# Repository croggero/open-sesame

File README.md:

# Open Sesame

ESP32-S3 firmware (Rust + esp-idf) for an assistive sliding door controller.

## Features

- Velocity-based assistive open/close
- Auto end-stop calibration and optional close-side homing
- Stall detection (obstacle / end-stop)
- Home Assistant MQTT discovery; commands, state and telemetry topics
- Captive-portal provisioning, factory reset via GPIO 0
- Build-time hardware/tuning configuration in `config.toml`

## Hardware

- ESP32-S3
- DRV8874 H-bridge (PhEn or InIn mode, set in `config.toml`)
- Quadrature encoder on the door drive
- Status LED, factory-reset button, optional toggle button

Pin assignments live under `[pins]` in `config.toml`.

## Building

Requires the Espressif Rust toolchain. See https://docs.esp-rs.org/book/installation/ for setup details.

1. Install `espup` and the `esp` toolchain:
   ```bash
   cargo install espup
   espup install
   ```
2. Source the export script in your shell (path printed by `espup install`):
   ```bash
   . $HOME/export-esp.sh
   ```
3. Install the flashing tools:
   ```bash
   cargo install espflash ldproxy
   ```
4. Edit `config.toml` to match your hardware (pins, motor mode, tuning).
5. Build:
   ```bash
   cargo build --release
   ```
6. Flash a connected ESP32 and open a serial monitor:
   ```bash
   cargo run --release
   ```
   Or, to flash with probe-rs and attach a debugger:
   ```bash
   cargo embed --release
   ```
  Or
  ```bash
  cargo flash --release --chip esp32s3
  ```

## First boot

1. Power the board. The status LED flashes to indicate the captive portal is active.
2. Connect to the `Open Sesame` SoftAP from a phone or laptop.
3. Submit WiFi and MQTT credentials in the provisioning form. The device reboots and connects.
4. The door is now visible in Home Assistant via MQTT discovery.

To re-provision, hold the factory-reset button (GPIO 0) for 5 seconds.

## Layout

- `src/main.rs` — boot sequence and control loop
- `src/door_controller.rs` — state machine, calibration, stall handling
- `src/motor.rs` — DRV8874 PWM driver (LEDC, 20 kHz)
- `src/encoder.rs` — PCNT quadrature decoder with 32-bit overflow tracking
- `src/mqtt_client.rs` — MQTT wrapper and command thread
- `src/captive_portal.rs` — SoftAP + HTTP provisioning
- `src/config.rs` — NVS-backed runtime config and build-time constants
- `config.toml` — hardware and tuning constants, parsed by `build.rs`

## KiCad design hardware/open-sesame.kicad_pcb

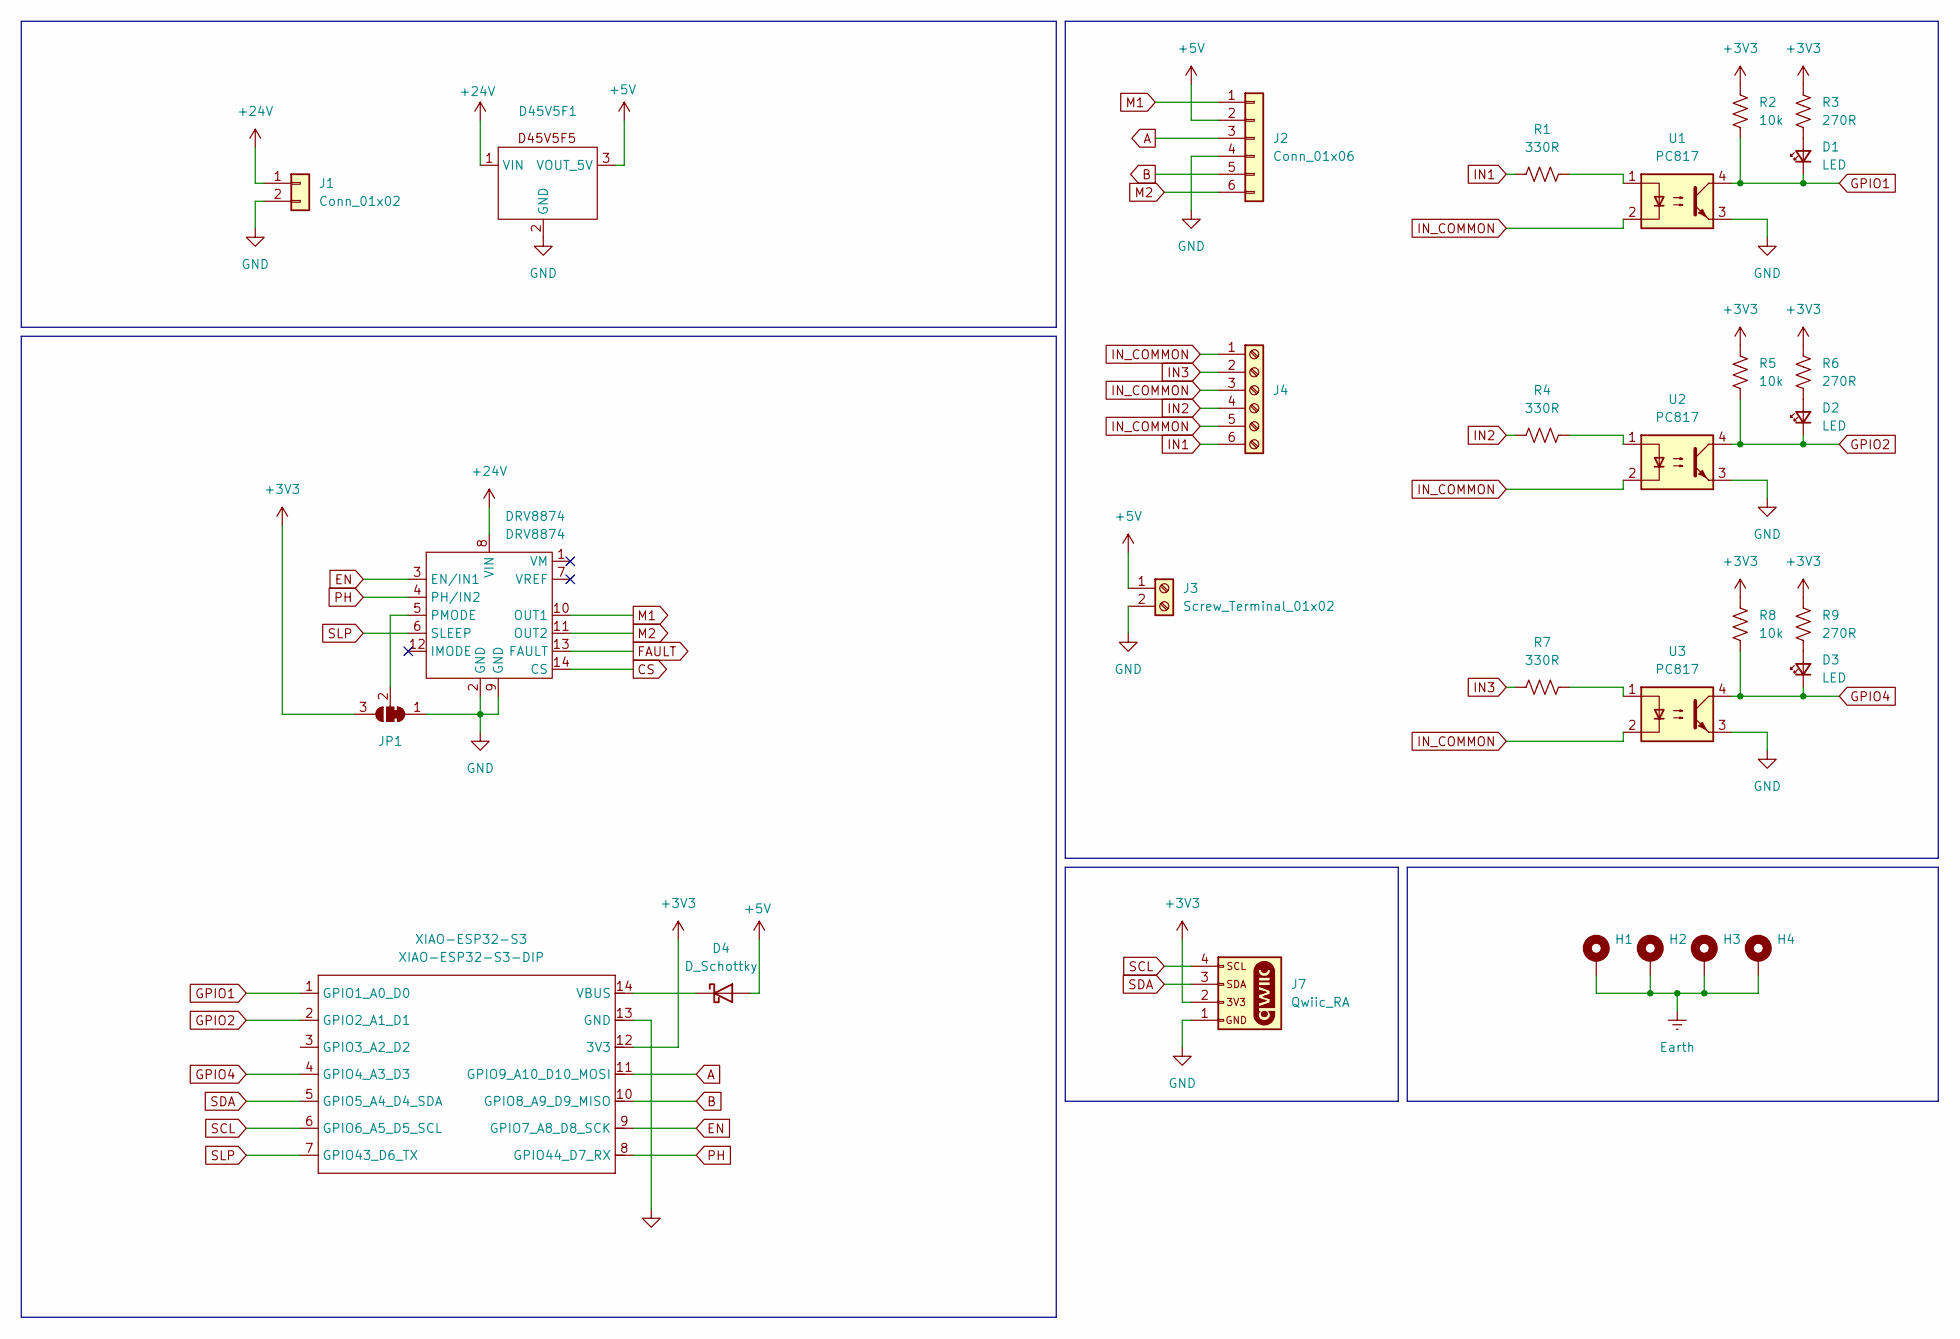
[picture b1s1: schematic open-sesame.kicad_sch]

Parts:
D1, D2, D3: LED; LED_0603_1608Metric
D4: D_Schottky; D_0603_1608Metric_Pad1.05x0.95mm_HandSolder
D45V5F1: D45V5F5; D45V5Fx
DRV8874: DRV8874
H1, H2, H3, H4: MountingHole_Pad; MountingHole_2.5mm_Pad_Via
J1: Conn_01x02; Molex_Nano-Fit_105313-xx02_1x02_P2.50mm_Horizontal
J2: Conn_01x06; Molex_Nano-Fit_105313-xx06_1x06_P2.50mm_Horizontal
J3: Screw_Terminal_01x02; TerminalBlock_Phoenix_MPT-0,5-2-2.54_1x02_P2.54mm_Horizontal
J4: Screw_Terminal_01x06; TerminalBlock_Phoenix_MPT-0,5-6-2.54_1x06_P2.54mm_Horizontal
J7: Qwiic_RA; JST_1x04_P1.0mm_Horizontal_SMD
JP1: SolderJumper_3_Bridged12; SolderJumper-3_P1.3mm_Bridged2Bar12_Pad1.0x1.5mm
R1, R4, R7: 330R; R_0603_1608Metric
R2, R5, R8: 10k; R_0603_1608Metric
R3, R6, R9: 270R; R_0603_1608Metric
U1, U2, U3: PC817; DIP-4_W7.62mm
XIAO-ESP32-S3: XIAO-ESP32-S3-DIP

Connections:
+3V3: J7.2, JP1.3 (B), R2.1, R3.1, R5.1, R6.1, R8.1, R9.1, XIAO-ESP32-S3.12 (3V3)
+5V: D4.2 (A), D45V5F1.3 (VOUT_5V), J2.2, J3.1
+24V: D45V5F1.1 (VIN), DRV8874.8 (VIN), J1.1
A: J2.3, XIAO-ESP32-S3.11 (GPIO9_A10_D10_MOSI)
B: J2.5, XIAO-ESP32-S3.10 (GPIO8_A9_D9_MISO)
CS: DRV8874.14 (CS)
EN: DRV8874.3 (EN/IN1), XIAO-ESP32-S3.9 (GPIO7_A8_D8_SCK)
Earth: H1.1, H2.1, H3.1, H4.1
FAULT: DRV8874.13 (FAULT)
GND: D45V5F1.2 (GND), DRV8874.2 (GND), DRV8874.9 (GND), J1.2, J2.4, J3.2, J7.1, JP1.1 (A), U1.3, U2.3, U3.3, XIAO-ESP32-S3.13 (GND)
GPIO1: D1.1 (K), R2.2, U1.4, XIAO-ESP32-S3.1 (GPIO1_A0_D0)
GPIO2: D2.1 (K), R5.2, U2.4, XIAO-ESP32-S3.2 (GPIO2_A1_D1)
GPIO4: D3.1 (K), R8.2, U3.4, XIAO-ESP32-S3.4 (GPIO4_A3_D3)
IN1: J4.6, R1.1
IN2: J4.4, R4.1
IN3: J4.2, R7.1
IN_COMMON: J4.1, J4.3, J4.5, U1.2, U2.2, U3.2
M1: DRV8874.10 (OUT1), J2.1
M2: DRV8874.11 (OUT2), J2.6
unnamed: D1.2 (A), R3.2
unnamed: D2.2 (A), R6.2
unnamed: D3.2 (A), R9.2
unnamed: D4.1 (K), XIAO-ESP32-S3.14 (VBUS)
unnamed: DRV8874.5 (PMODE), JP1.2 (C)
unnamed: R1.2, U1.1
unnamed: R4.2, U2.1
unnamed: R7.2, U3.1
PH: DRV8874.4 (PH/IN2), XIAO-ESP32-S3.8 (GPIO44_D7_RX)
SCL: J7.4, XIAO-ESP32-S3.6 (GPIO6_A5_D5_SCL)
SDA: J7.3, XIAO-ESP32-S3.5 (GPIO5_A4_D4_SDA)
SLP: DRV8874.6 (SLEEP), XIAO-ESP32-S3.7 (GPIO43_D6_TX)

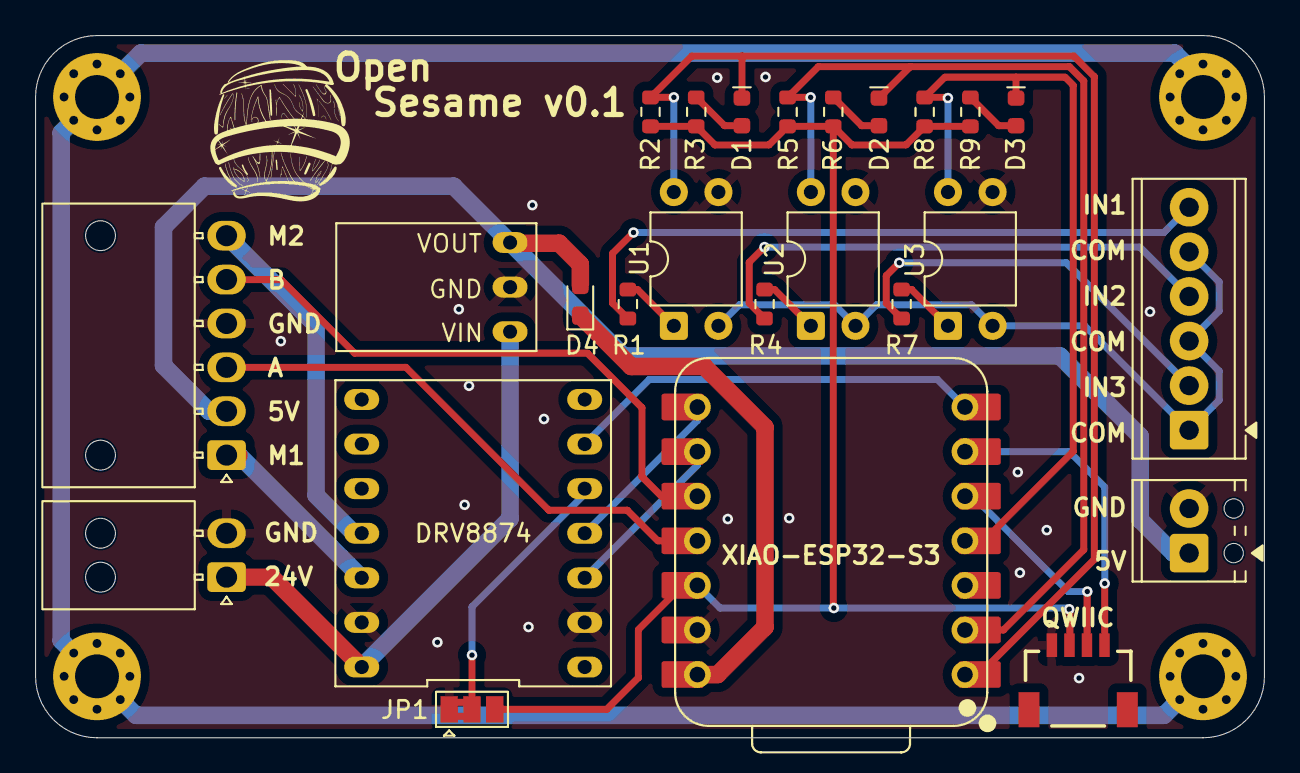
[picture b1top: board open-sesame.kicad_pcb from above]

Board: 2 copper layers, 70.0 x 40.0 mm, 29 parts (0 on the bottom side), 29 nets.

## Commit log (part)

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2026-02-05 Initial hardware circuit
2026-02-05 Added .gitignore
2026-02-05 Updated 3V & GND to terminal block
2026-02-05 fix(hardware): Corrected VIN&VOUT
2026-02-25 User Terminals, Added Optocoupler, Added QWIIC connector
2026-02-25 Use 2x 6 port connectors
2026-02-28 hardware: Use ESP32S3 for PCNT,
2026-03-02 hardware: shrunk board
2026-03-06 hardware: Use screw connectors and PC817
2026-03-24 hardware: use one power converter, shrink size, change connectors
2026-03-27 firmware: Initial Firmware
2026-03-31 firmware: Added calibration, obstacle stall detection, HA discovery, toggle pin
2026-03-31 firmware: set position via percentage
2026-03-31 firmware: fix invert direction, added homing, save opening counts
2026-04-02 firmware: added homing, adjusted parameters, closed threshold
2026-05-03 firmware: increase max duty
2026-05-03 firmware: mDNS support, MQTT publish thread separation, Wifi auto reconnect.
2026-05-03 firmware: added .gitignore
2026-05-03 Created README.md
